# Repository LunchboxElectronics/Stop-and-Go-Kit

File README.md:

# README #

Stop and Go Kit by Lunchbox Electronics. 2015

### What is this repository for? ###

This repo supplies instructions and source files to create and make derivatives of the Stop and Go Kit. This kit is programmed to be a simple stoplight with an ATtiny and Build Upons PTH Edition. Compatible with LEGO sets. This repo contains:

* Eagle Files
* Instructions
* Gif

### How do I get set up? ###

* Code is written in Arduino
* Board File and Schematic are created in Eagle

### Licensing ###
Stop and Go kit is an open source hardware product and follows the open source hardware definition: www.oshwa.org/definition The Eagle Files are licensed CC-BY-SA: Lunchbox Electronics.

### Warrenty ###
Distributed as-is; no warranty given. Not suitable for people who might eat electronics.

### Who do I talk to? ###

* Created by Jason Brownstein @ Lunchbox Electronics 5/6/15
* Contact contact@lunchboxelectronics.com

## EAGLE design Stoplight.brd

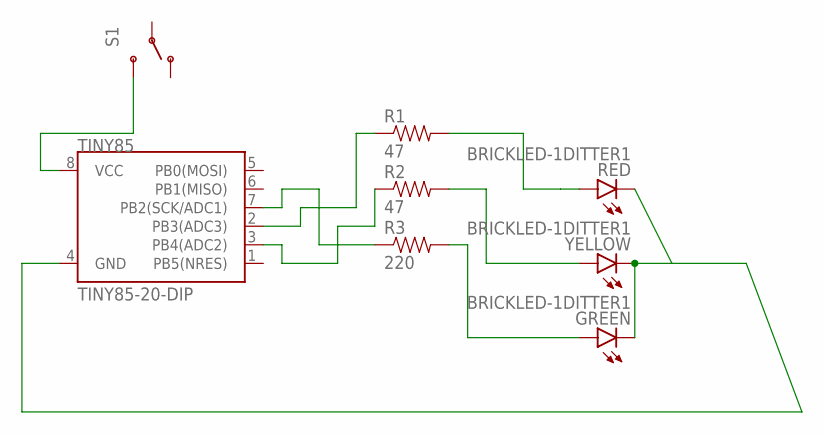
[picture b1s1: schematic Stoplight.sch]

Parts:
GREEN: BRICKLED-1DITTER1; BRICKLED-1DITTER
R1, R2: 47; AXIAL-0.3
R3: 220; AXIAL-0.3
RED: BRICKLED-1DITTER1; BRICKLED-1DITTER
S1: SWITCH-SPDTKIT; SWITCH-SPDT_KIT
TINY85: TINY85-20-DIP; DIP08
YELLOW: BRICKLED-1DITTER1; BRICKLED-1DITTER

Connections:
unnamed: S1.3 (S), TINY85.8 (VCC)
unnamed: R1.P$2 (2), RED.A
unnamed: GREEN.K (C), RED.K (C), TINY85.4 (GND), YELLOW.K (C)
unnamed: R1.P$1 (1), TINY85.2 (PB3(ADC3))
unnamed: R2.P$1 (1), TINY85.3 (PB4(ADC2))
unnamed: GREEN.A, R3.P$2 (2)
unnamed: R2.P$2 (2), YELLOW.A
unnamed: R3.P$1 (1), TINY85.7 (PB2(SCK/ADC1))

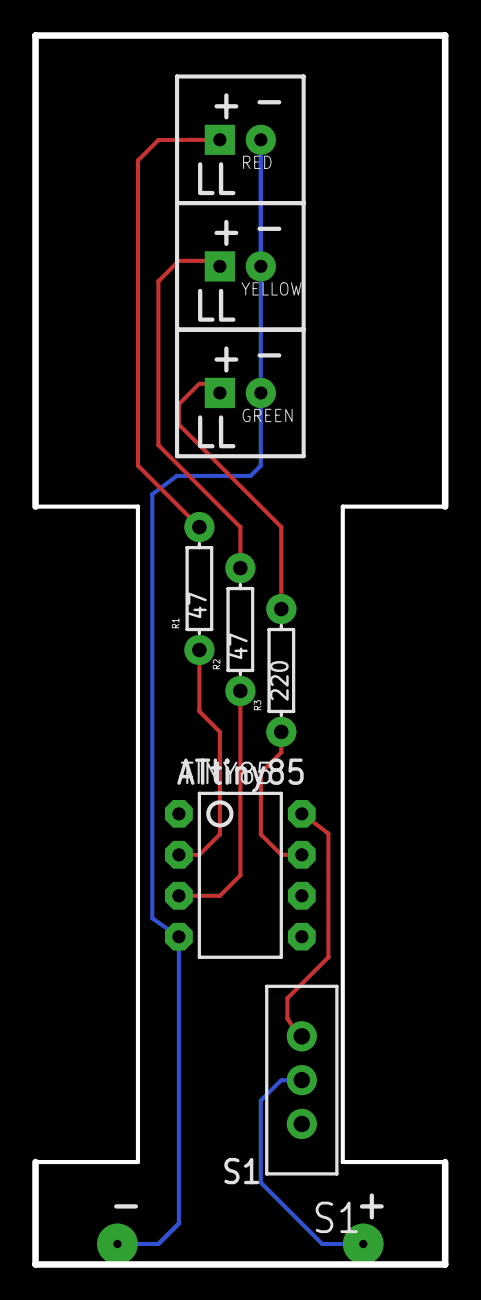
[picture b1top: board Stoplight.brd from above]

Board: 2 copper layers, 25.4 x 76.2 mm, 8 parts (0 on the bottom side), 8 nets.

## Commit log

2016-04-27 Adding files

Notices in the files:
parts and their libraries:
SparkFun-Resistors: Licensing: Creative Commons ShareAlike 4.0 International - https://creativecommons.org/licenses/by-sa/4.0
